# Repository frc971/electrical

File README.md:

This repo contains the electrical files for the 971 FRC team.
The files include PCBs and the electrical system diagrams.
The PCBs are created using KiCad.

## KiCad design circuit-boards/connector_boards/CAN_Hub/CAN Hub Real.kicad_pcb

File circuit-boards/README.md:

# PCB Catalog

Table Of Contents
1. [Beam Break Board](#beam-break-board)
    * [Features](#features-1)
    * [Specifications](#specifications)
    * [Applications](#applications)
        * [Compatibility](#compatibility)
2. [Spartan Board](#spartan-board)
    * [Features](#features-2)
3. [Encoder Adapter Board](#encoder-adapter-board)
    * [Features](#features-3)
4. [Mag Encoder Adapter Board](#mag-encoder-adapter-board)
    * [Features](#features-4)
5. [Potentiometer Adapter Board](#potentiometer-adapter-board)
    * [Features](#features-5)
6. [CAN Terminator](#can-terminator)
    * [Features](#features-6)
7. [Mini Power Distribution Board](#mini-power-distribution-board)
    * [Features](#features-7)
    * [Specifications](#specifications-2)
        * [Rated Current](#rated-current)
8. [Kraken CAN Connector Board](#kraken-can-connector-board)
    * [Features](#features-8)

---

## Beam Break Board

### Features
* Interfaces industrial beam break sensors to the RoboRio
* Utilizes optocoupler to increase signal integrity by preventing ground loops
* Power and Signal LEDs to aid in user diagnostics
* Single-sided design for easy mounting and fabrication

### Specifications
* Active Low Output
* 12V Power
* Molex SL Connectors

### Applications
* Beam Break
* Other sensors with similar active low (NPN) output signal

  #### Compatibility
  * Sensors or switching devices with similar Output to Automation Direct QMI7-0N-0F
  * Compatible with Spartan Board

---

## Spartan Board

### Features
* Converts all RoboRio connections to latching Molex SL connectors
* Quick and straightforward installation
* Labeled Ports
* All through-hole connectors for easy re-work/replacement and reliability
* 13x Digital I/O ports
* 8x Analog Input ports
* 6x Quadrature Encoder Input Ports
* 6x Combined Encoder, Analog Input, PWM Input Ports
* 10x PWM Outputs
* 4x SPI Ports
* I2C Bus
* RS232 Console
* RSL Port

---

## Encoder Adapter Board

### Features
* Connects 5-pin optical encoder (US Digital [S1-512-250-IE-B-D](https://www.usdigital.com/products/encoders/incremental/shaft/s1/)) to a Molex SL connector 
* Power indication LED 
* Compatible with Spartan Board

---

## Mag Encoder Adapter Board

### Features
* Connects 3-pin [3549S-1BA-102B potentiometer](https://www.digikey.com/en/products/detail/bourns-inc/3549S-1BA-102B/2534314) and 10-pin [CTRE mag encoder](https://store.ctr-electronics.com/srx-mag-encoder/) to a 6-pin Molex SL connector
* Compatible with Spartan Board
* Power indication LED 

---

## Potentiometer Adapter Board

### Features
* Connects 3-pin [3549S-1BA-102B potentiometer](https://www.digikey.com/en/products/detail/bourns-inc/3549S-1BA-102B/2534314) 3 to 10 turn potentiometers to a Molex SL connector 
* Power indication LED 
* Compatible with Spartan Board

---

## CAN Terminator

### Features
* 120 Ohm CAN bus terminator using a 2 pin Molex SL connector

---

## Mini Power Distribution Board

### Features
* LED lights up when a fuse is inserted. 
* Replaceable fuses
* Labeled connectors   

### Specifications
* 12-24 AWG output WAGO connectors
* 8-24AWG input WAGO connectors
* [MINI® 297 fuses](https://www.littelfuse.com/products/fuses/automotive-passenger-car/blade-fuses/297.aspx)
* Max current is 10 amps per circuit

---

## Kraken CAN Connector Board

### Features
* Molex SL connectors
* Simplifies connecting Kraken motors to a CAN bus

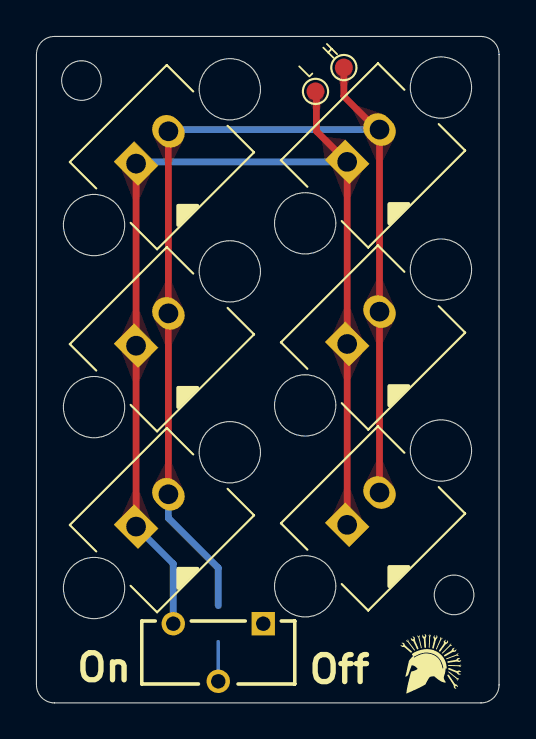
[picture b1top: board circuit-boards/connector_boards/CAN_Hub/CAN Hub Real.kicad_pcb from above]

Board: 2 copper layers, 25.7 x 37.0 mm, 12 parts (1 on the bottom side), 3 nets.

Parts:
H1, H2: MountingHole; MountingHole_2.2mm_M2
J1, J2, J3, J4, J5, J6: Conn_01x02_Pin; 70541-0001
R1: 120R; R_0805_2012Metric_Pad1.20x1.40mm_HandSolder
S1: JS102011CQN
TP1: TP_G; TestPoint_Pad_D1.0mm
TP2: TP_Y; TestPoint_Pad_D1.0mm

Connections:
/CAN_H: J1.2, J2.2, J3.2, J4.2, J5.2, J6.2, R1.1, TP2.1 (1_1)
/CAN_L: J1.1, J2.1, J3.1, J4.1, J5.1, J6.1, S1.3 (NO), TP1.1 (1_1)
unnamed: R1.2, S1.2 (COM)

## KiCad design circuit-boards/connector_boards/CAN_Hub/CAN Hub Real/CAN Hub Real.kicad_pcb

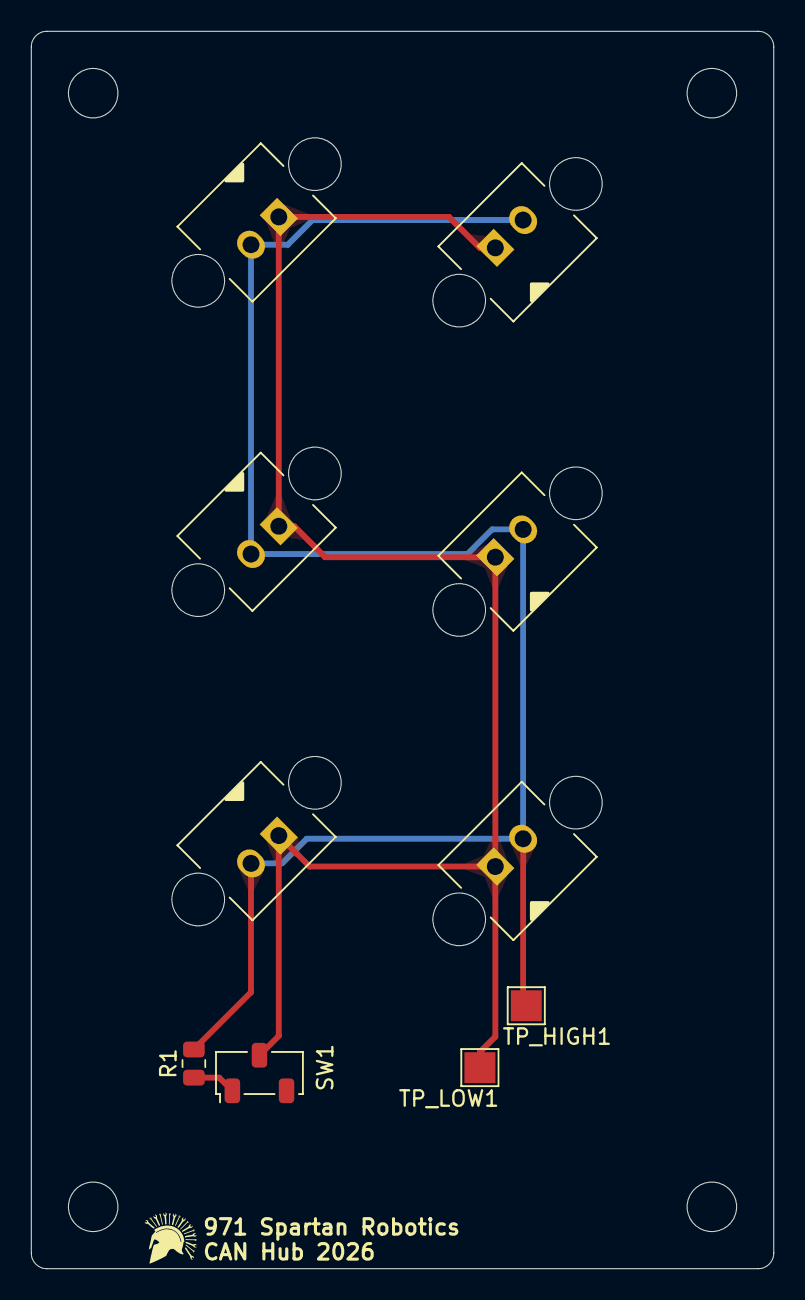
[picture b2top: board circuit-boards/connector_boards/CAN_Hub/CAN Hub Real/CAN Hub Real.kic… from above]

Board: 2 copper layers, 48.0 x 80.0 mm, 14 parts (0 on the bottom side), 2 nets.

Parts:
H1, H2, H3, H4: MountingHole; MountingHole_3.2mm_M3
J1, J2, J3, J4, J5, J6: Conn_01x02_Pin; 70541-0001
R1: 120R; R_0805_2012Metric
SW1: TERMINATOR; Nidec_Copal_CAS-120A
TP_HIGH1: TestPoint; TestPoint_Pad_2.0x2.0mm
TP_LOW1: TestPoint; TestPoint_Pad_2.0x2.0mm

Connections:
/CAN_H: J1.2, J2.2, J3.2, J4.2, J5.2, J6.2, R1.2, TP_HIGH1.1 (1_1)
/CAN_L: J1.1, J2.1, J3.1, J4.1, J5.1, J6.1, R1.1, SW1.1 (C), SW1.2 (B), TP_LOW1.1 (1_1)

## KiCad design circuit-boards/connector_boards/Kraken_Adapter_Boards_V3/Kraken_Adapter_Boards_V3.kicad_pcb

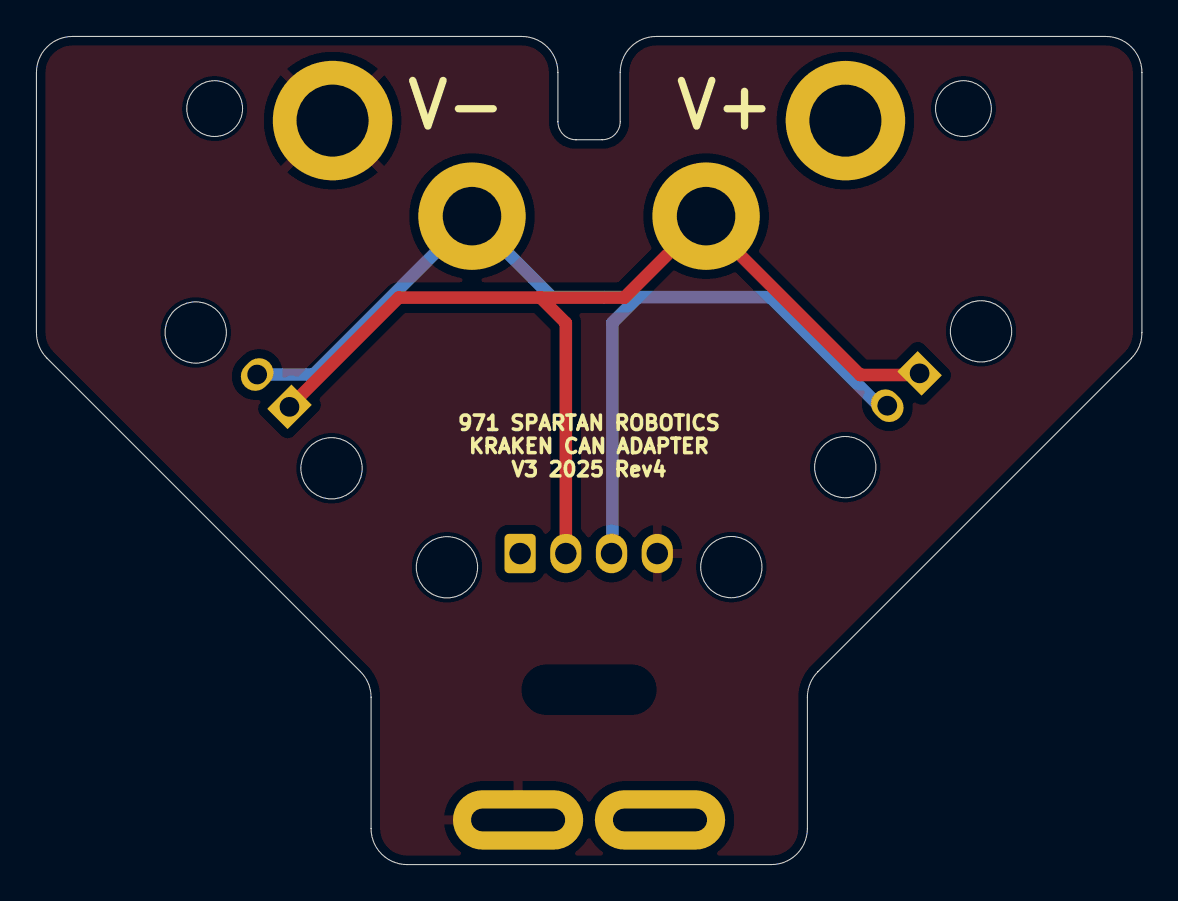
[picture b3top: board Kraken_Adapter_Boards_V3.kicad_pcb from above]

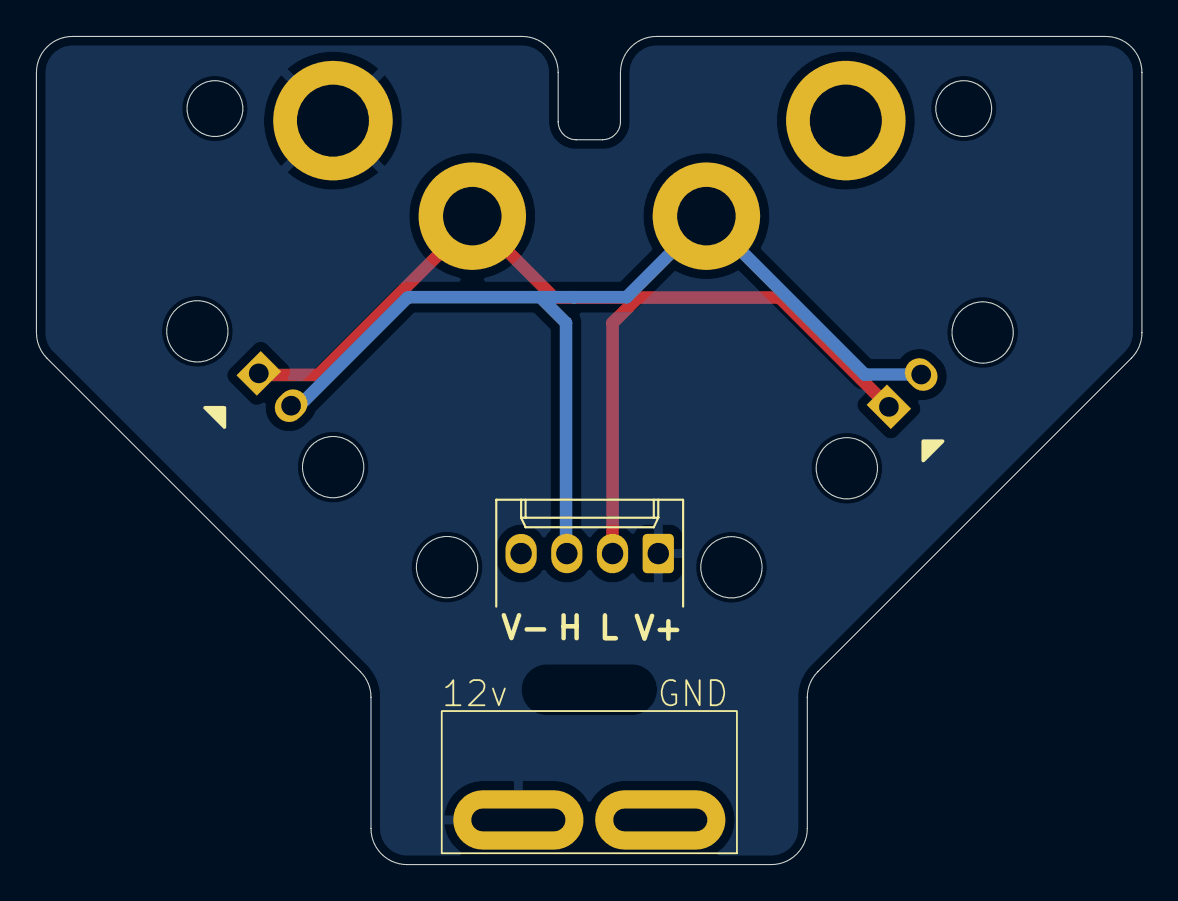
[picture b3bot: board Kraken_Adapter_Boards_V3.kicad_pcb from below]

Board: 2 copper layers, 61.4 x 46.0 mm, 10 parts (4 on the bottom side), 4 nets.

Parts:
J3: can_l_mount; can_x60
J4: can_h_mount; can_x60
J7: pwr_mount; pwr_krk
J8: gnd_mount; pwr_krk
M8: enclosure mount; pwr_krk
M8#2: mount; pwr_krk
anderson1: pwr_output; krk_pwr_board_housing
molex1: can_output; Molex_KK-254_AE-6410-02A_1x02_P2.54mm_Vertical_lock_mod
molex2: can_input; Molex_KK-254_AE-6410-02A_1x02_P2.54mm_Vertical_lock_mod
molex3: can_pwr_node_housing; Molex_KK-254_AE-6410-04A_1x04_P2.54mm_Vertical

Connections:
+12V: J7.1, anderson1.2, molex3.1
/can_h: J4.1, molex1.2, molex2.2, molex3.3
/can_l: J3.1, molex1.1, molex2.1, molex3.2
GND: J8.1, anderson1.1, molex3.4

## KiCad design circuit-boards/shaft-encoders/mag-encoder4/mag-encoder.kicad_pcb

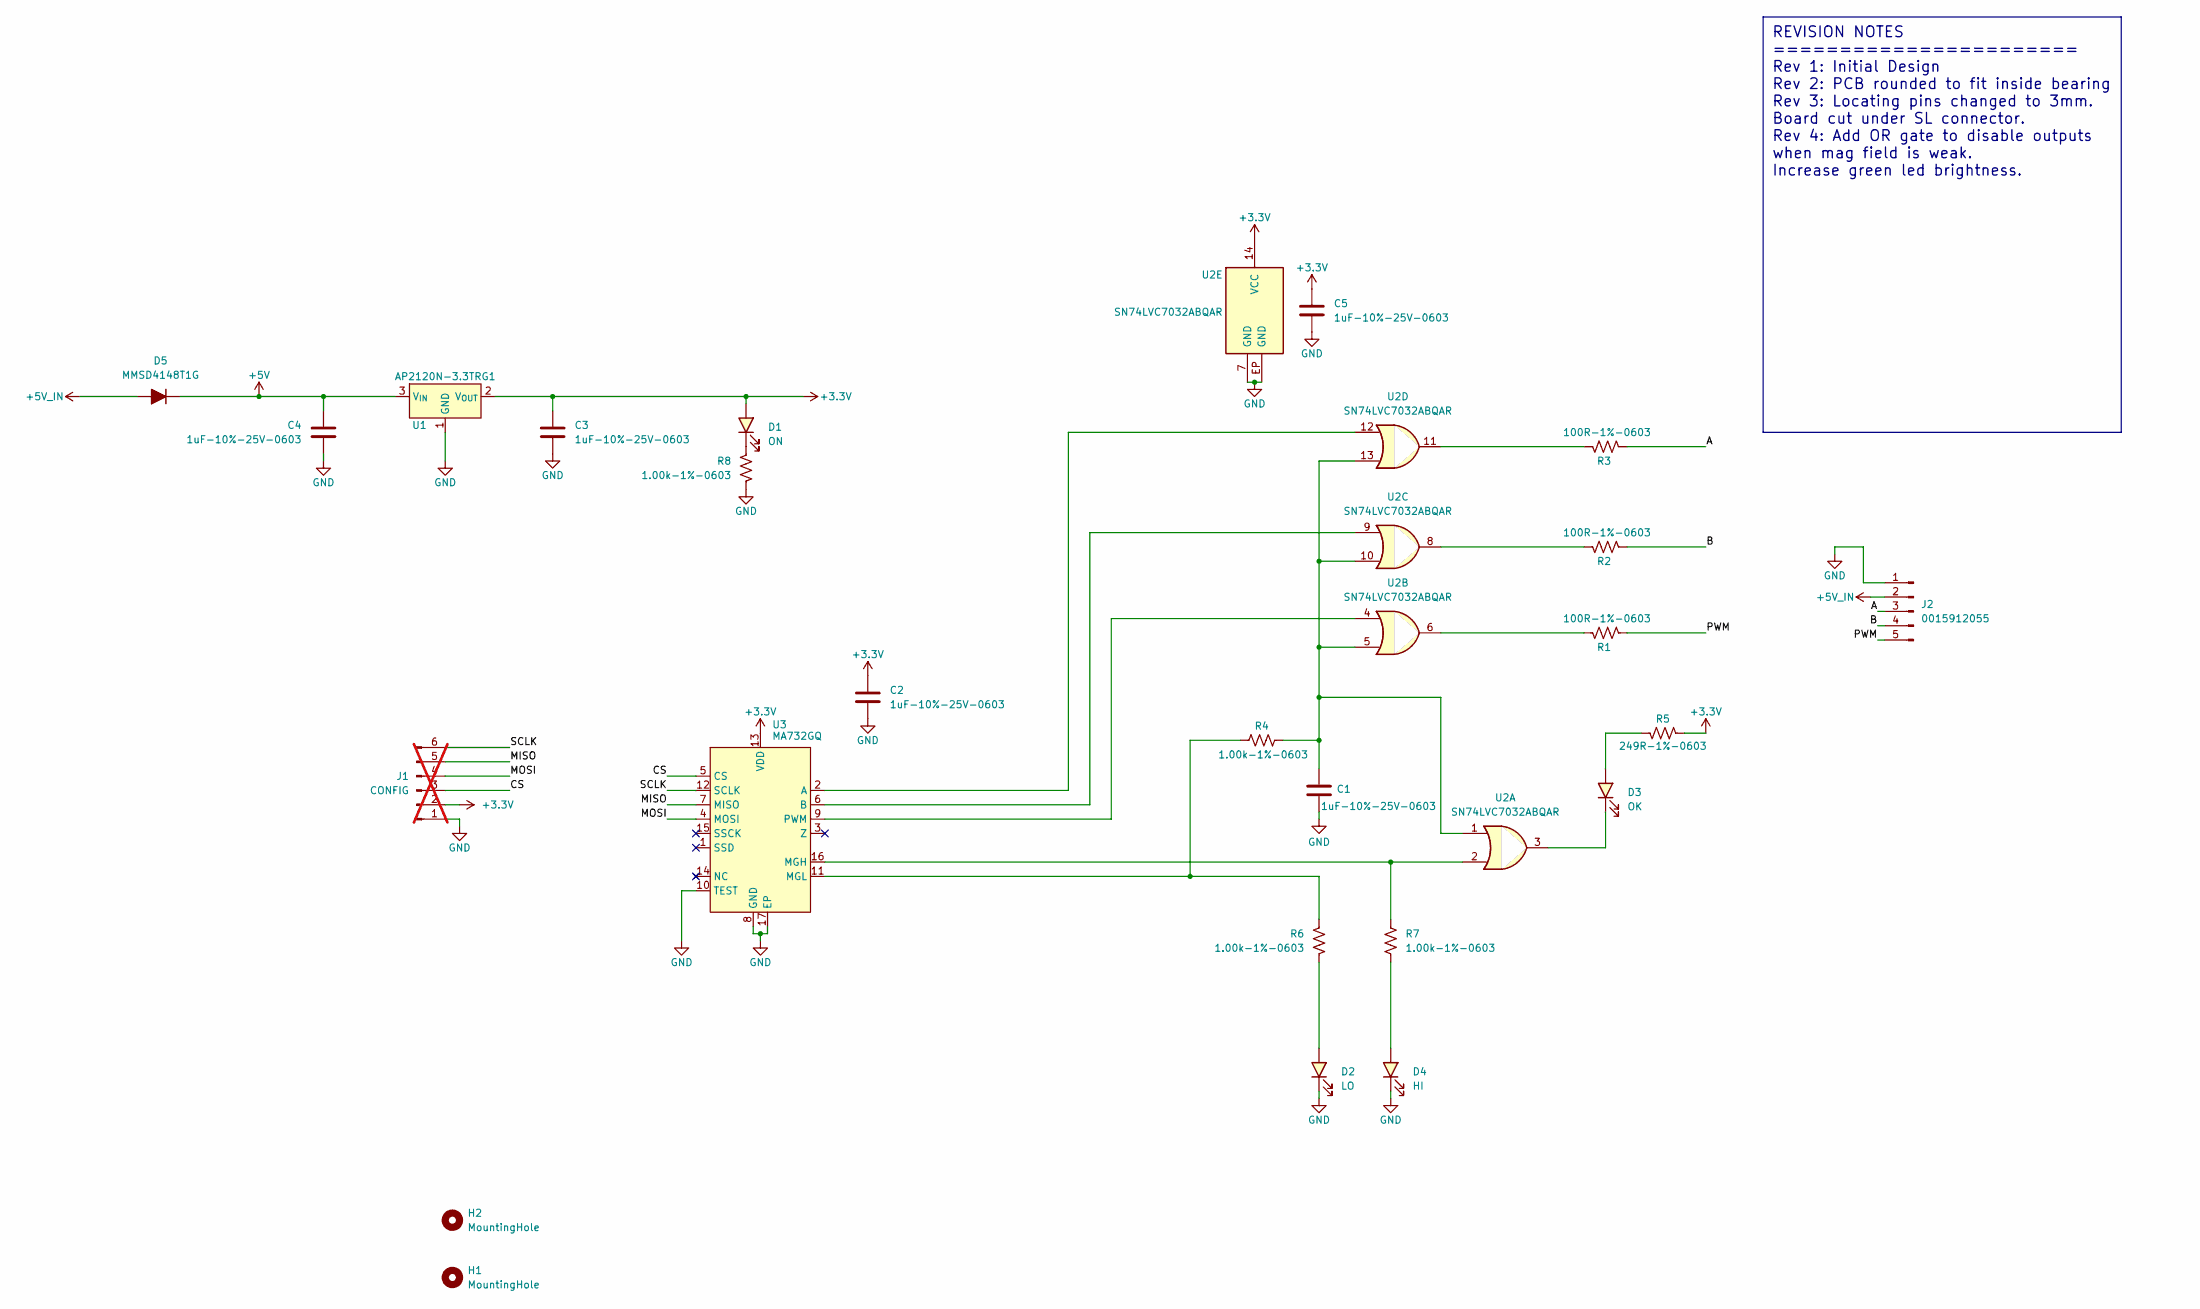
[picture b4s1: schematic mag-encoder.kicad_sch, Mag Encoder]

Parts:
C1, C2, C3, C4, C5: 1uF-10%-25V-0603; C_0603_1608Metric; MFG P/N 06033C105KAT2A
D1: ON; LED_0603_1608Metric; MFG P/N 150060YS75000
D2: LO; LED_0603_1608Metric; MFG P/N 150060RS75000
D3: OK; LED_0603_1608Metric; MFG P/N 150060VS75000
D4: HI; LED_0603_1608Metric; MFG P/N 150060RS75000
D5: MMSD4148T1G; D_SOD-123; MFG P/N MMSD4148T1G
H1, H2: MountingHole; pin-0.100
J1: CONFIG; PinHeader_1x06_P2.54mm_Vertical; not fitted
J2: 0015912055; Molex-70634-0039; MFG P/N 0015912055
R1, R2, R3: 100R-1%-0603; R_0603_1608Metric; MFG P/N RC0603FR-07100RL
R4, R6, R7, R8: 1.00k-1%-0603; R_0603_1608Metric; MFG P/N RC0603FR-071KL
R5: 249R-1%-0603; R_0603_1608Metric; MFG P/N RC0603FR-07249RL
U1: AP2120N-3.3TRG1; SOT-23; MFG P/N AP2120N-3.3TRG1
U2: SN74LVC7032ABQAR; TI-WQFN-14-1EP_2.5x3mm_EP_1x1.5mm; MFG P/N SN74LVC7032ABQAR
U3: MA732GQ; QFN-16-1EP_3x3mm_P0.5mm_EP1.7x1.7mm; MFG P/N MA732GQ-Z

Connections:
+3.3V: C2.1, C3.1, C5.1, D1.2 (A), J1.2, R5.1, U1.2 (V_{OUT}), U2.14 (VCC), U3.13 (VDD)
+5V: C4.1, D5.1 (K), U1.3 (V_{IN})
+5V_IN: D5.2 (A), J2.2
/A: J2.3, R3.2
/B: J2.4, R2.2
/CS: J1.3, U3.5 (CS)
/MISO: J1.5, U3.7 (MISO)
/MOSI: J1.4, U3.4 (MOSI)
/PWM: J2.5, R1.2
/SCLK: J1.6, U3.12 (SCLK)
GND: C1.2, C2.2, C3.2, C4.2, C5.2, D2.1 (K), D4.1 (K), J1.1, J2.1, R8.2, U1.1 (GND), U2.7 (GND), U2.EP (GND), U3.8 (GND), U3.10 (TEST), U3.17 (EP)
unnamed: C1.1, R4.2, U2.1, U2.5, U2.10, U2.13
unnamed: D1.1 (K), R8.1
unnamed: D2.2 (A), R6.2
unnamed: D3.2 (A), R5.2
unnamed: D3.1 (K), U2.3
unnamed: D4.2 (A), R7.2
unnamed: R1.1, U2.6
unnamed: R2.1, U2.8
unnamed: R3.1, U2.11
unnamed: U2.12, U3.2 (A)
unnamed: U2.9, U3.6 (B)
unnamed: R7.1, U2.2, U3.16 (MGH)
unnamed: R4.1, R6.1, U3.11 (MGL)
unnamed: U2.4, U3.9 (PWM)

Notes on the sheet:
REVISION NOTES ======================= Rev 1: Initial Design Rev 2: PCB rounded to fit inside bearing Rev 3: Locating pins changed to 3mm. Board cut under SL connector. Rev 4: Add OR gate to disable outputs when mag field is weak. Increase green led brightness.

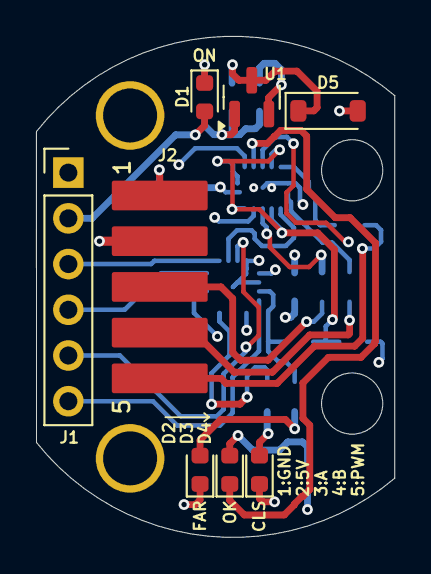
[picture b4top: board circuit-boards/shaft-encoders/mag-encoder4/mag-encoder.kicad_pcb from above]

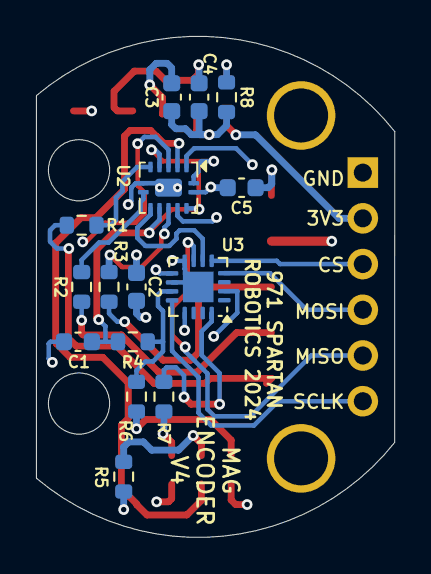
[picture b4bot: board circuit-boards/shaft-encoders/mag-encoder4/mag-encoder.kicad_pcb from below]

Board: 4 copper layers, 19.9 x 27.8 mm, 25 parts (15 on the bottom side), 25 nets.

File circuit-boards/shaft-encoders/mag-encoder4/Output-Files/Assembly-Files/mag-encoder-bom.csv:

"Item","QUANTITY","Reference","Value","MFG","MFG P/N","DIST","DIST P/N"
"1","5","C1-C5","1uF-10%-25V-0603","Kyocera","06033C105KAT2A","Digikey","478-10046-1-ND"
"2","1","D1","ON","Wurth Electronik","150060YS75000","Digikey","732-4981-1-ND"
"3","1","D3","OK","Wurth Electronik","150060VS75000","Digikey","732-4980-1-ND"
"4","1","D5","MMSD4148T1G","onsemi","MMSD4148T1G","Digikey","MMSD4148T1GOSCT-ND"
"5","2","D2,D4","-- mixed values --","Wurth Electronik","150060RS75000","Digikey","732-4978-1-ND"
"6","1","J2","0015912055","Molex","0015912055","Digikey","WM1343-ND"
"7","1","R5","249R-1%-0603","YAGEO","RC0603FR-07249RL","Digikey","311-249HRCT-ND"
"8","3","R1-R3","100R-1%-0603","YAGEO","RC0603FR-07100RL","Digikey","311-100HRCT-ND"
"9","4","R4,R6-R8","1.00k-1%-0603","YAGEO","RC0603FR-071KL","Digikey","311-1.00KHRCT-ND"
"10","1","U1","AP2120N-3.3TRG1","Diodes Inc","AP2120N-3.3TRG1","Digikey","AP2120N-3.3TRG1DICT-ND"
"11","1","U2","SN74LVC7032ABQAR","Texas Instruments","SN74LVC7032ABQAR","Digikey","296-SN74LVC7032ABQARCT-ND"
"12","1","U3","MA732GQ","Monolithic Power Systems","MA732GQ-Z","Digikey","1589-MA732GQ-ZCT-ND"

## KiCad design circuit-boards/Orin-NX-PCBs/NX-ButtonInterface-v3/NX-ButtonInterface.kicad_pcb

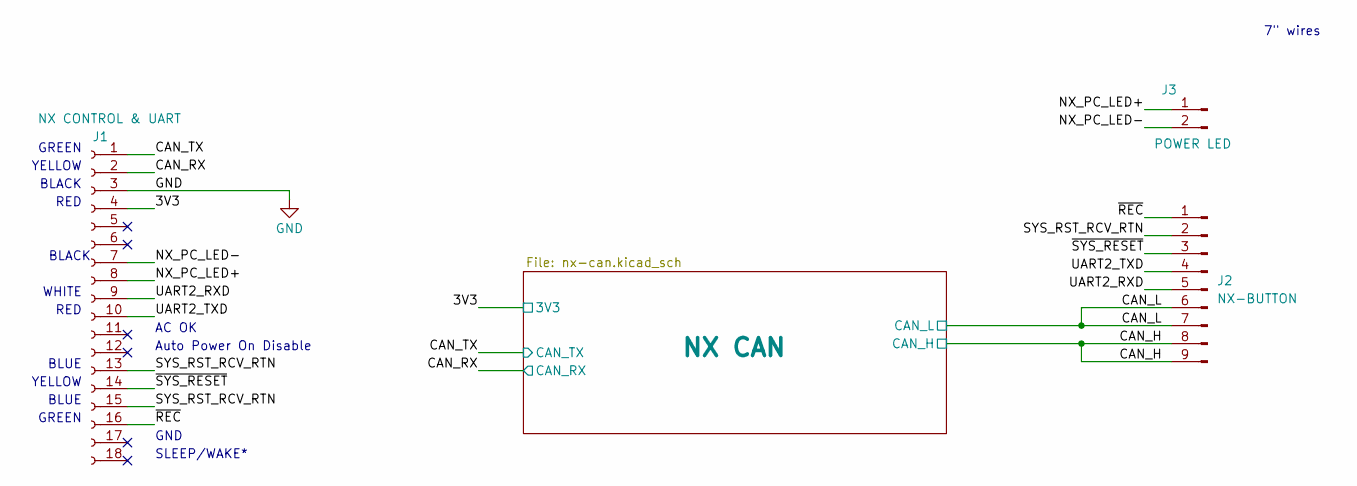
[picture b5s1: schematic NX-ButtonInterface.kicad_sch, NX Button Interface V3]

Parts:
J1: NX CONTROL & UART; PinSocket_1x18_P2.54mm_Vertical; MFG P/N PPTC181LFBN-RC
J2: NX-BUTTON; 9-pin-solder-pads
J3: POWER LED; 2-pin-solder-pads

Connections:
/3V3: J1.4; also elsewhere on the board
/CAN_H: J2.8, J2.9; also elsewhere on the board
/CAN_L: J2.6, J2.7; also elsewhere on the board
/CAN_RX: J1.2; also elsewhere on the board
/CAN_TX: J1.1; also elsewhere on the board
/NX_PC_LED+: J1.8, J3.1
/NX_PC_LED-: J1.7, J3.2
/SYS_RST_RCV_RTN: J1.13, J1.15, J2.2
/UART2_RXD: J1.9, J2.5
/UART2_TXD: J1.10, J2.4
/~REC: J1.16, J2.1
/~SYS_RESET: J1.14, J2.3
GND: J1.3; also elsewhere on the board

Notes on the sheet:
RED
YELLOW
GREEN
BLACK
WHITE
BLUE
7" wires
AC OK
GND
Auto Power On Disable
SLEEP/WAKE*

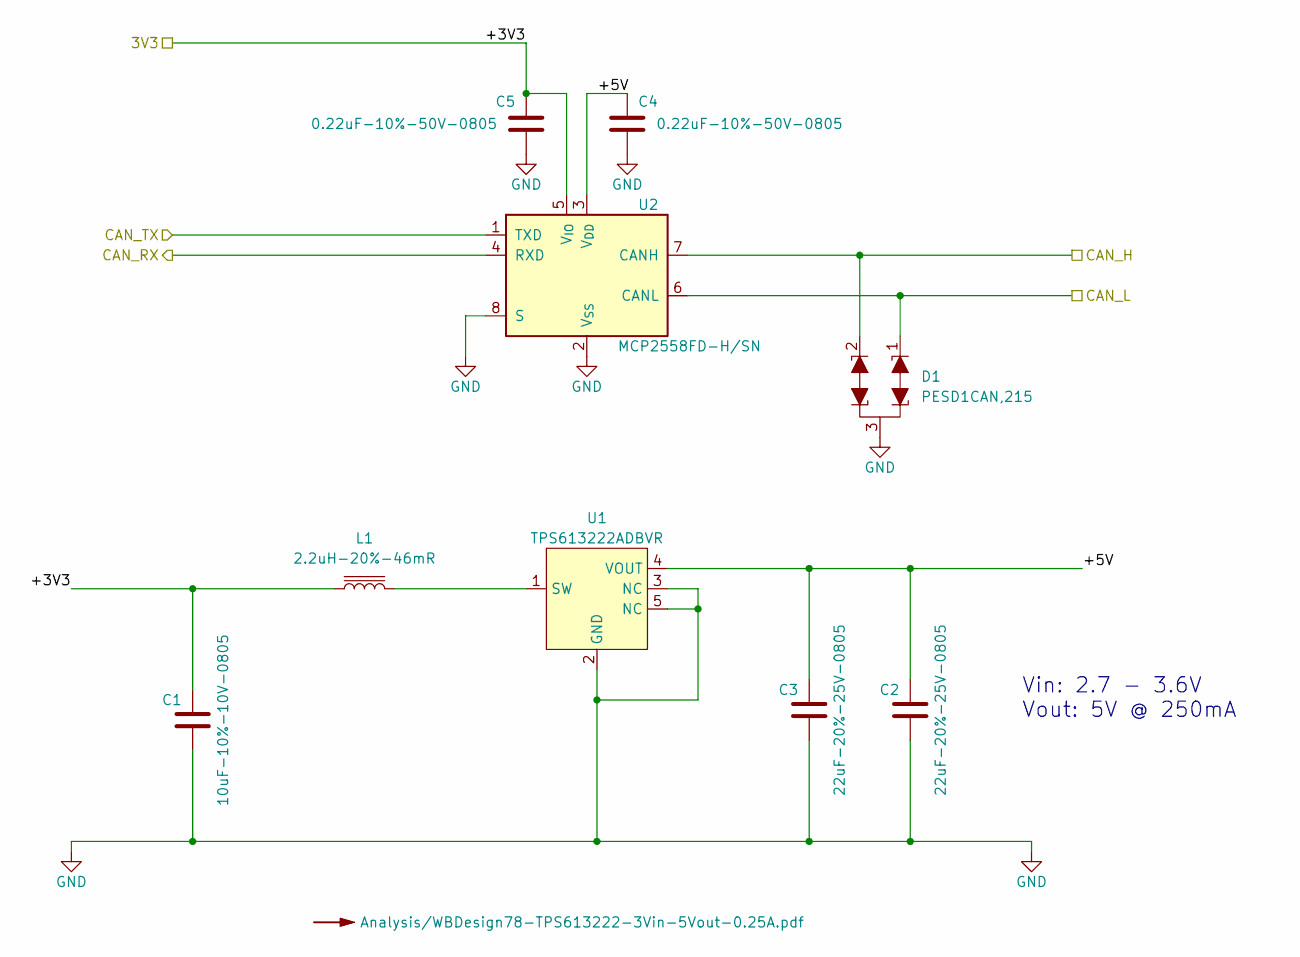
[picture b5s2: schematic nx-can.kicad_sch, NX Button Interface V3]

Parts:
C1: 10uF-10%-10V-0805; C_0805_2012Metric; MFG P/N C0805C106K8PAC7800
C2, C3: 22uF-20%-25V-0805; C_0805_2012Metric; MFG P/N CL21A226MAYNNNE
C4, C5: 0.22uF-10%-50V-0805; C_0805_2012Metric; MFG P/N C0805C224K5RAC7800
D1: PESD1CAN; SOT-23; MFG P/N PESD1CAN,215
L1: 2.2uH-20%-46mR; L_Vishay_IHLP-1212; MFG P/N IHLP1212BZER2R2M11
U1: TPS613222ADBVR; SOT-23-5; MFG P/N TPS613222ADBVR
U2: MCP2558FD-H/SN; SOIC-8_3.9x4.9mm_P1.27mm; MFG P/N MCP2558FD-H/SN

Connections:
/3V3: C1.1, C5.1, L1.1, U2.5 (V_{IO}); also elsewhere on the board
/CAN_H: D1.2 (K1), U2.7 (CANH); also elsewhere on the board
/CAN_L: D1.1 (K1), U2.6 (CANL); also elsewhere on the board
/CAN_RX: U2.4 (RXD); also elsewhere on the board
/CAN_TX: U2.1 (TXD); also elsewhere on the board
/NX CAN/+5V: C2.1, C3.1, C4.1, U1.4 (VOUT), U2.3 (V_{DD})
GND: C1.2, C2.2, C3.2, C4.2, C5.2, D1.3 (KK), U1.2 (GND), U1.3 (NC), U1.5 (NC), U2.2 (V_{SS}), U2.8 (S); also elsewhere on the board
unnamed: L1.2, U1.1 (SW)

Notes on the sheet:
Vin: 2.7 - 3.6V Vout: 5V @ 250mA

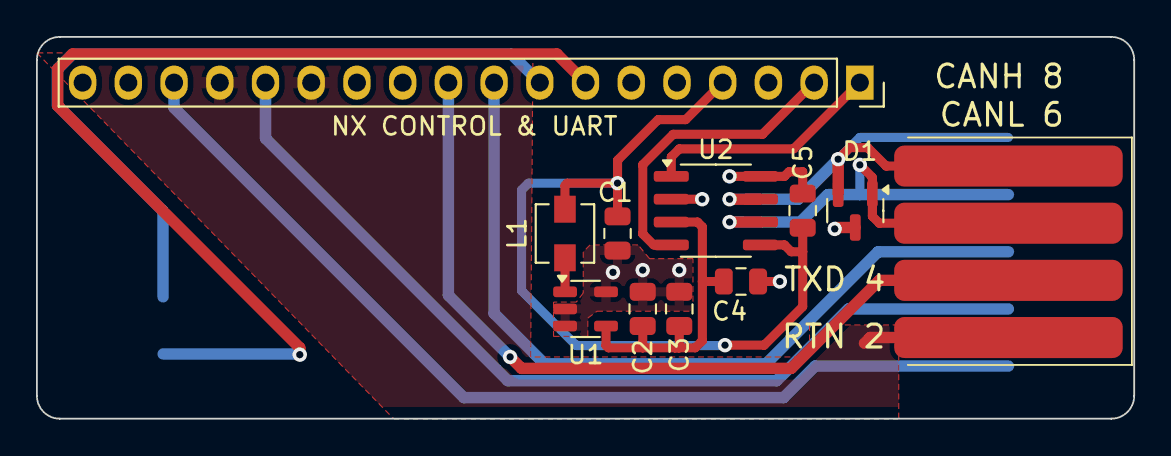
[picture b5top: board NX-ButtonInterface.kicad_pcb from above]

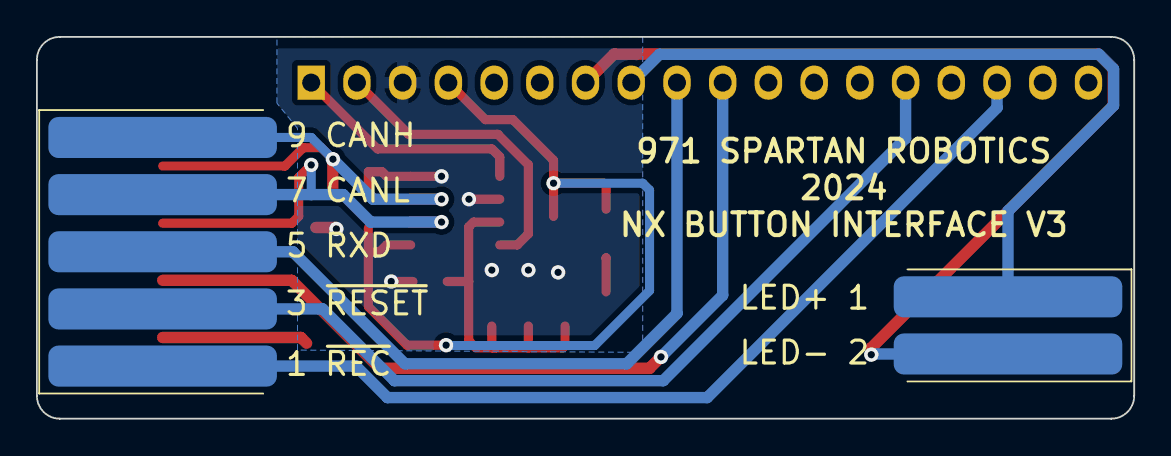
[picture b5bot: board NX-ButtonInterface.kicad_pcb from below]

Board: 2 copper layers, 61.0 x 21.2 mm, 12 parts (2 on the bottom side), 15 nets.

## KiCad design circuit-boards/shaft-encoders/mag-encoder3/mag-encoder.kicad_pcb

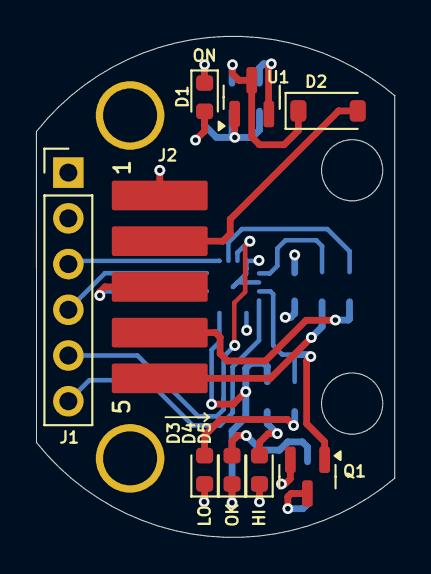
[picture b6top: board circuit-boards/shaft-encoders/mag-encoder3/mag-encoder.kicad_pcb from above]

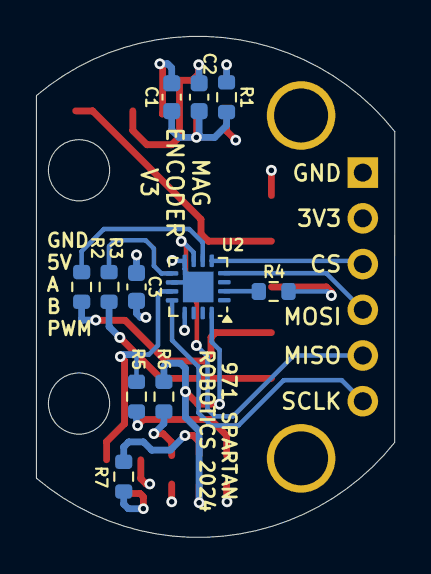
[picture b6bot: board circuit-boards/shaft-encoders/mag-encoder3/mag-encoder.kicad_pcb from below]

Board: 4 copper layers, 19.9 x 27.8 mm, 22 parts (11 on the bottom side), 21 nets.

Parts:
C1, C2, C3: 1uF-10%-25V-0603; C_0603_1608Metric
D1: ON; LED_0603_1608Metric
D2: MMSD4148T1G; D_SOD-123
D3: LO; LED_0603_1608Metric
D4: OK; LED_0603_1608Metric
D5: HI; LED_0603_1608Metric
H1, H2: MountingHole; pin-0.100
J1: CONFIG; PinHeader_1x06_P2.54mm_Vertical
J2: 0015912055; Molex-70634-0039
Q1: BSS84; SOT-23
R1, R5, R6, R7: 1.00k-1%-0603; R_0603_1608Metric
R2, R3, R4: 100R-1%-0603; R_0603_1608Metric
U1: AP2120N-3.3TRG1; SOT-23
U2: MA732GQ; QFN-16-1EP_3x3mm_P0.5mm_EP1.7x1.7mm

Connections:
+3.3V: C1.1, C3.1, D1.2 (A), J1.2, Q1.2 (S), U1.2 (V_{OUT}), U2.13 (VDD)
+5V: C2.1, D2.1 (K), U1.3 (V_{IN})
+5V_IN: D2.2 (A), J2.2
/A: J2.3, R4.2
/B: J2.4, R2.2
/CS: J1.3, U2.5 (CS)
/MISO: J1.5, U2.7 (MISO)
/MOSI: J1.4, U2.4 (MOSI)
/PWM: J2.5, R3.2
/SCLK: J1.6, U2.12 (SCLK)
GND: C1.2, C2.2, C3.2, D3.1 (K), D5.1 (K), J1.1, J2.1, R1.2, U1.1 (GND), U2.8 (GND), U2.10 (TEST), U2.17 (EP)
unnamed: D1.1 (K), R1.1
unnamed: D3.2 (A), R5.2
unnamed: D4.2 (A), R7.2
unnamed: D4.1 (K), R6.1, U2.16 (MGH)
unnamed: D5.2 (A), R6.2
unnamed: Q1.3 (D), R7.1
unnamed: Q1.1 (G), R5.1, U2.11 (MGL)
unnamed: R4.1, U2.2 (A)
unnamed: R2.1, U2.6 (B)
unnamed: R3.1, U2.9 (PWM)

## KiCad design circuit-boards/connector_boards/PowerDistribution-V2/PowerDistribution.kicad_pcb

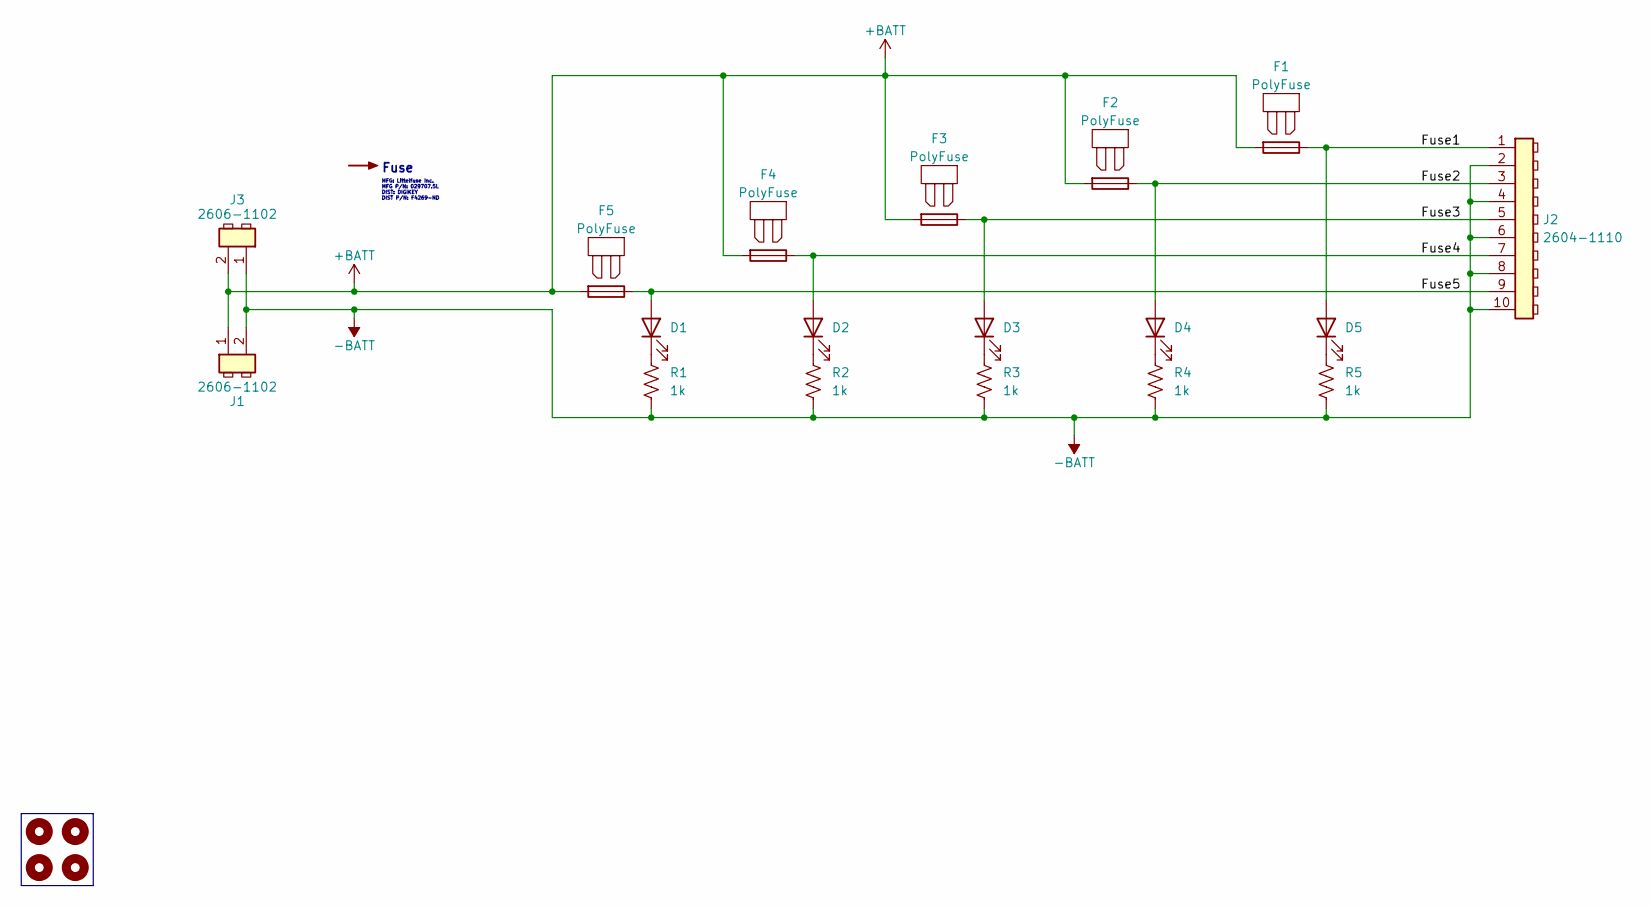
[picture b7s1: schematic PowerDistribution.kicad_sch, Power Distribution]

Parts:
D1, D2, D3, D4, D5: QTLP651C4TR; LED_1206_3216Metric_Pad1.42x1.75mm_HandSolder; MFG P/N QTLP651C4TR
F1, F2, F3, F4, F5: PolyFuse; FUSE_3568; MFG P/N 3568
H1, H2, H5, H6: MountingHole; MountingHole_2.2mm_M2_DIN965_Pad
J1, J3: 2606-1102; 2606-1102&slash_000-005; MFG P/N 2606-1102
J2: 2604-1110; MFG P/N 2604-1110
R1, R2, R3, R4, R5: 1k; R_1206_3216Metric_Pad1.30x1.75mm_HandSolder; MFG P/N RMCF1206FT1K00

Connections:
+BATT: F1.2, F2.2, F3.2, F4.2, F5.2, J1.1, J3.2
-BATT: J1.2, J2.2, J2.4, J2.6, J2.8, J2.10, J3.1, R1.2, R2.2, R3.2, R4.2, R5.2
/Fuse1: D5.2 (A), F1.1, J2.1
/Fuse2: D4.2 (A), F2.1, J2.3
/Fuse3: D3.2 (A), F3.1, J2.5
/Fuse4: D2.2 (A), F4.1, J2.7
/Fuse5: D1.2 (A), F5.1, J2.9
unnamed: D1.1 (K), R1.1
unnamed: D2.1 (K), R2.1
unnamed: D3.1 (K), R3.1
unnamed: D4.1 (K), R4.1
unnamed: D5.1 (K), R5.1

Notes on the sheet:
Fuse
MFG: Littelfuse Inc. MFG P/N: 029707.5L DIST: DIGIKEY DIST P/N: F4269-ND

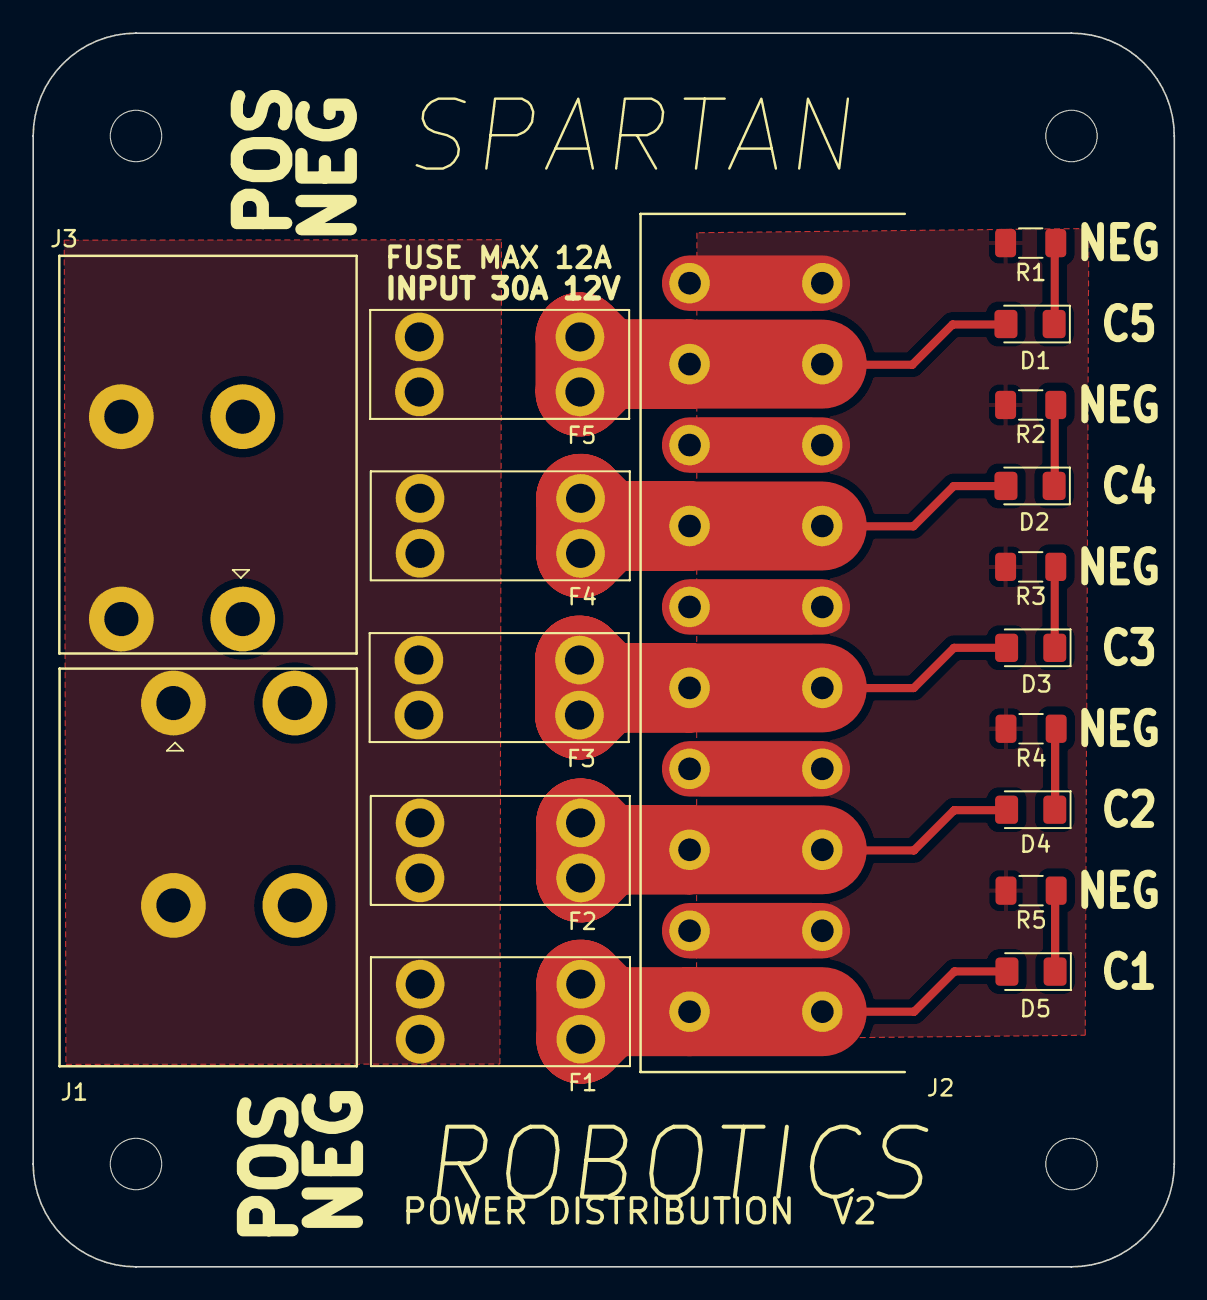
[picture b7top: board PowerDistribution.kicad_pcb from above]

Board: 2 copper layers, 70.5 x 76.2 mm, 22 parts (0 on the bottom side), 12 nets.

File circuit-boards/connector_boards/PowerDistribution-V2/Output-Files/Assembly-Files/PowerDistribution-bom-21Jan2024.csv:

Item, Qty, Reference(s), Value, DIST, DIST P/N, LINK, Link, MFG, MFG P/N, 
"1","5","D1,D2,D3,D4,D5","QTLP651C4TR","DIGIKEY","QTLP651C4TR","https://www.digikey.com/en/products/detail/everlight-electro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","","Everlight Electronics Co Ltd","QTLP651C4TR"
"2","5","F1,F2,F3,F4,F5","PolyFuse","DIGIKEY","36-3568-ND","https://www.digikey.com/en/products/detail/keystone-electron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","","Keystone Electronics","3568"
"3","1","J1","2606-1102","DIGIKEY","2946-2606-1102-ND","https://www.digikey.com/en/products/detail/wago-corporation/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","https://www.digikey.com/en/products/detail/wago-corporation/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","WAGO","2606-1102"
"4","1","J2","2604-1110","DIGIKEY","2946-2604-1110-ND","https://www.digikey.com/en/products/detail/wago-corporation/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","","WAGO","2604-1110"
"5","5","R1,R2,R3,R4,R5","1k","DIGIKEY","RMCF1206FT1K00","https://www.digikey.com/en/products/detail/stackpole-electro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","","Stackpole Electronics Inc","RMCF1206FT1K00"

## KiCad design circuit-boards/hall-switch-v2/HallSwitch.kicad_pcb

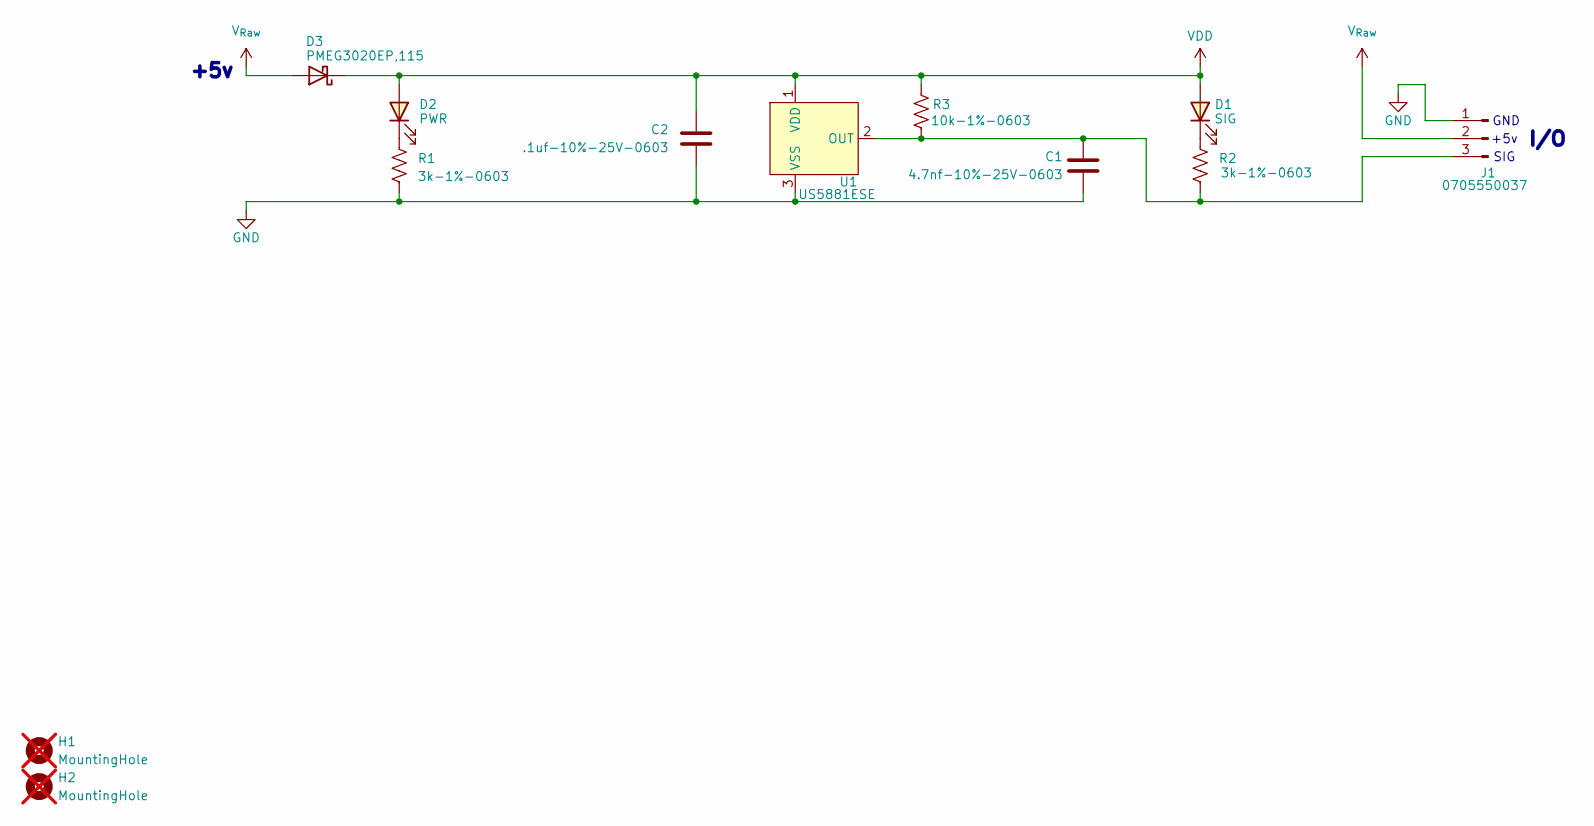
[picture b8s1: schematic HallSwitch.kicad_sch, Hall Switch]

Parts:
C1: 4.7nf-10%-25V-0603; C_0603_1608Metric; MFG P/N C0603C472K3RAC7867
C2: .1uf-10%-25V-0603; C_0603_1608Metric; MFG P/N C0603C104K3RAC7867
D1: SIG; LED_1206_3216Metric; MFG P/N XZVG55W-A2RT
D2: PWR; LED_1206_3216Metric; MFG P/N XZVG55W-A2RT
D3: PMEG3020EP,115; D_SOD-128; MFG P/N 1727-5836-1-ND
H1, H2: MountingHole; MountingHole_2.1mm; not fitted
J1: 0705550037; 70555-0037; MFG P/N 0705550037
R1, R2: 3k-1%-0603; R_0603_1608Metric; MFG P/N ERA-3AEB302VRMCF0603FT3K00
R3: 10k-1%-0603; R_0603_1608Metric; MFG P/N RC0603FR-0710KL
U1: US5881ESE; SOT-23-3; MFG P/N US5881ESE-AAA-000-RECT-ND

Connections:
GND: C1.2, C2.2, J1.1, R1.2, U1.3 (VSS)
unnamed: D1.1 (K), R2.1
unnamed: D2.1 (K), R1.1
unnamed: C1.1, J1.3, R2.2, R3.2, U1.2 (OUT)
VDD: C2.1, D1.2 (A), D2.2 (A), D3.1 (K), R3.1, U1.1 (VDD)
V_{Raw}: D3.2 (A), J1.2

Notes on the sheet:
GND
SIG
+5v
I/O
+5v

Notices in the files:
parts and their libraries:
Copyright 2021 Accelerated Designs. All rights reserved.
Copyright 2016 Accelerated Designs. All rights reserved.
